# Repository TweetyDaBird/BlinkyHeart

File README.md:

# BlinkyRGB
Blinky RGB Keychains in various shapes and sizes.

Uses an Microchip ATTINY85 MCU, and is powered by a CR2032 coin cell.

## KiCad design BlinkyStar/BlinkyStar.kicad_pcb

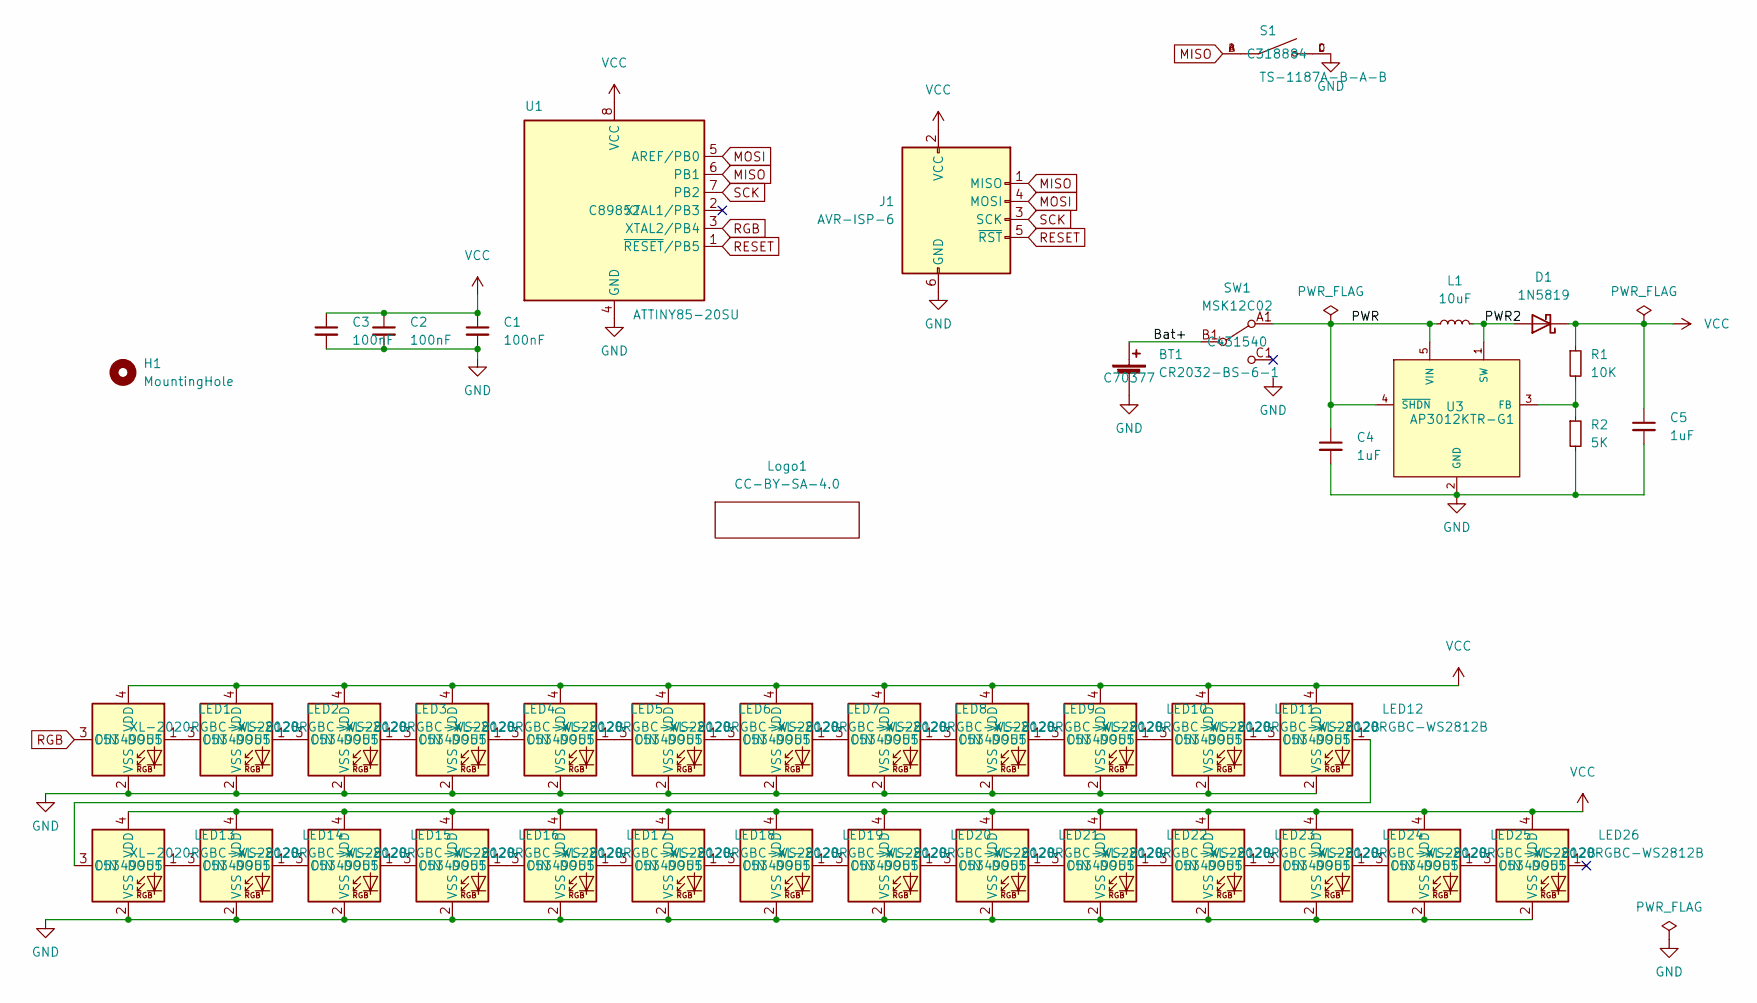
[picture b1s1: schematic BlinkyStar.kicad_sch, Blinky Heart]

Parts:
BT1: CR2032-BS-6-1; BAT_CR2032-BS-6-1; LCSC C70377
C1, C2, C3: 100nF; C_0603_1608Metric_Pad1.08x0.95mm_HandSolder; LCSC C14663
C4, C5: 1uF; C_0603_1608Metric_Pad1.08x0.95mm_HandSolder; LCSC C15849
D1: 1N5819; D_SMA; LCSC C437199
H1: MountingHole; MountingHole_3.2mm_M3
J1: AVR-ISP-6; PinHeader_2x03_P2.54mm_Vertical
L1: 10uF; IND_FDSD0420-H-100M=P3; LCSC C1329533
LED1, LED2, LED3, LED4, LED5, LED6, LED7, LED8, LED9, LED10, LED11, LED12, LED13, LED14, LED15, LED16, LED17, LED18, LED19, LED20, LED21, LED22, LED23, LED24, LED25, LED26: XL-2020RGBC-WS2812B; LED_WS2812-2020; LCSC C5349955
Logo1: CC-BY-SA-4.0; CC_BY_SA_40
R1: 10K; R_0603_1608Metric_Pad0.98x0.95mm_HandSolder; LCSC C3017715
R2: 5K; R_0603_1608Metric_Pad0.98x0.95mm_HandSolder; LCSC C2828621
S1: TS-1187A-B-A-B; SW_TS-1187A-B-A-B; PARTREV A0; LCSC C318884
SW1: MSK12C02; LCSC C431540
U1: ATTINY85-20SU; SOIC-8W_5.3x5.3mm_P1.27mm; LCSC C89852
U3: AP3012KTR-G1; SOT95P280X145-5N; PARTREV 1.6; LCSC C102618

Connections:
/Bat+: BT1.1 (+), SW1.B1 (COM)
/PWR: C4.1, L1.1, SW1.A1 (A), U3.4 (~SHDN), U3.5 (VIN)
/PWR2: D1.2 (A), L1.2, U3.1 (SW)
GND: BT1.2 (-), C1.2, C2.2, C3.2, C4.2, C5.2, J1.6 (GND), LED1.2 (VSS), LED2.2 (VSS), LED3.2 (VSS), LED4.2 (VSS), LED5.2 (VSS), LED6.2 (VSS), LED7.2 (VSS), LED8.2 (VSS), LED9.2 (VSS), LED10.2 (VSS), LED11.2 (VSS), LED12.2 (VSS), LED13.2 (VSS), LED14.2 (VSS), LED15.2 (VSS), LED16.2 (VSS), LED17.2 (VSS), LED18.2 (VSS), LED19.2 (VSS), LED20.2 (VSS), LED21.2 (VSS), LED22.2 (VSS), LED23.2 (VSS), LED24.2 (VSS), LED25.2 (VSS), LED26.2 (VSS), R2.2, S1.C, S1.D, SW1.MP (GND), U1.4 (GND), U3.2 (GND)
MISO: J1.1 (MISO), S1.A, S1.B, U1.6 (PB1)
MOSI: J1.4 (MOSI), U1.5 (AREF/PB0)
unnamed: LED1.1 (DOUT), LED2.3 (DIN)
unnamed: LED2.1 (DOUT), LED3.3 (DIN)
unnamed: LED3.1 (DOUT), LED4.3 (DIN)
unnamed: LED4.1 (DOUT), LED5.3 (DIN)
unnamed: LED5.1 (DOUT), LED6.3 (DIN)
unnamed: LED6.1 (DOUT), LED7.3 (DIN)
unnamed: LED7.1 (DOUT), LED8.3 (DIN)
unnamed: LED8.1 (DOUT), LED9.3 (DIN)
unnamed: LED10.1 (DOUT), LED11.3 (DIN)
unnamed: LED9.1 (DOUT), LED10.3 (DIN)
unnamed: LED11.1 (DOUT), LED12.3 (DIN)
unnamed: LED12.1 (DOUT), LED13.3 (DIN)
unnamed: LED13.1 (DOUT), LED14.3 (DIN)
unnamed: LED14.1 (DOUT), LED15.3 (DIN)
unnamed: LED15.1 (DOUT), LED16.3 (DIN)
unnamed: LED16.1 (DOUT), LED17.3 (DIN)
unnamed: LED17.1 (DOUT), LED18.3 (DIN)
unnamed: LED18.1 (DOUT), LED19.3 (DIN)
unnamed: LED19.1 (DOUT), LED20.3 (DIN)
unnamed: LED20.1 (DOUT), LED21.3 (DIN)
unnamed: LED21.1 (DOUT), LED22.3 (DIN)
unnamed: LED22.1 (DOUT), LED23.3 (DIN)
unnamed: LED23.1 (DOUT), LED24.3 (DIN)
unnamed: LED24.1 (DOUT), LED25.3 (DIN)
unnamed: LED25.1 (DOUT), LED26.3 (DIN)
unnamed: R1.2, R2.1, U3.3 (FB)
RESET: J1.5 (~RST), U1.1 (~RESET/PB5)
RGB: LED1.3 (DIN), U1.3 (XTAL2/PB4)
SCK: J1.3 (SCK), U1.7 (PB2)
VCC: C1.1, C2.1, C3.1, C5.1, D1.1 (K), J1.2 (VCC), LED1.4 (VDD), LED2.4 (VDD), LED3.4 (VDD), LED4.4 (VDD), LED5.4 (VDD), LED6.4 (VDD), LED7.4 (VDD), LED8.4 (VDD), LED9.4 (VDD), LED10.4 (VDD), LED11.4 (VDD), LED12.4 (VDD), LED13.4 (VDD), LED14.4 (VDD), LED15.4 (VDD), LED16.4 (VDD), LED17.4 (VDD), LED18.4 (VDD), LED19.4 (VDD), LED20.4 (VDD), LED21.4 (VDD), LED22.4 (VDD), LED23.4 (VDD), LED24.4 (VDD), LED25.4 (VDD), LED26.4 (VDD), R1.1, U1.8 (VCC)

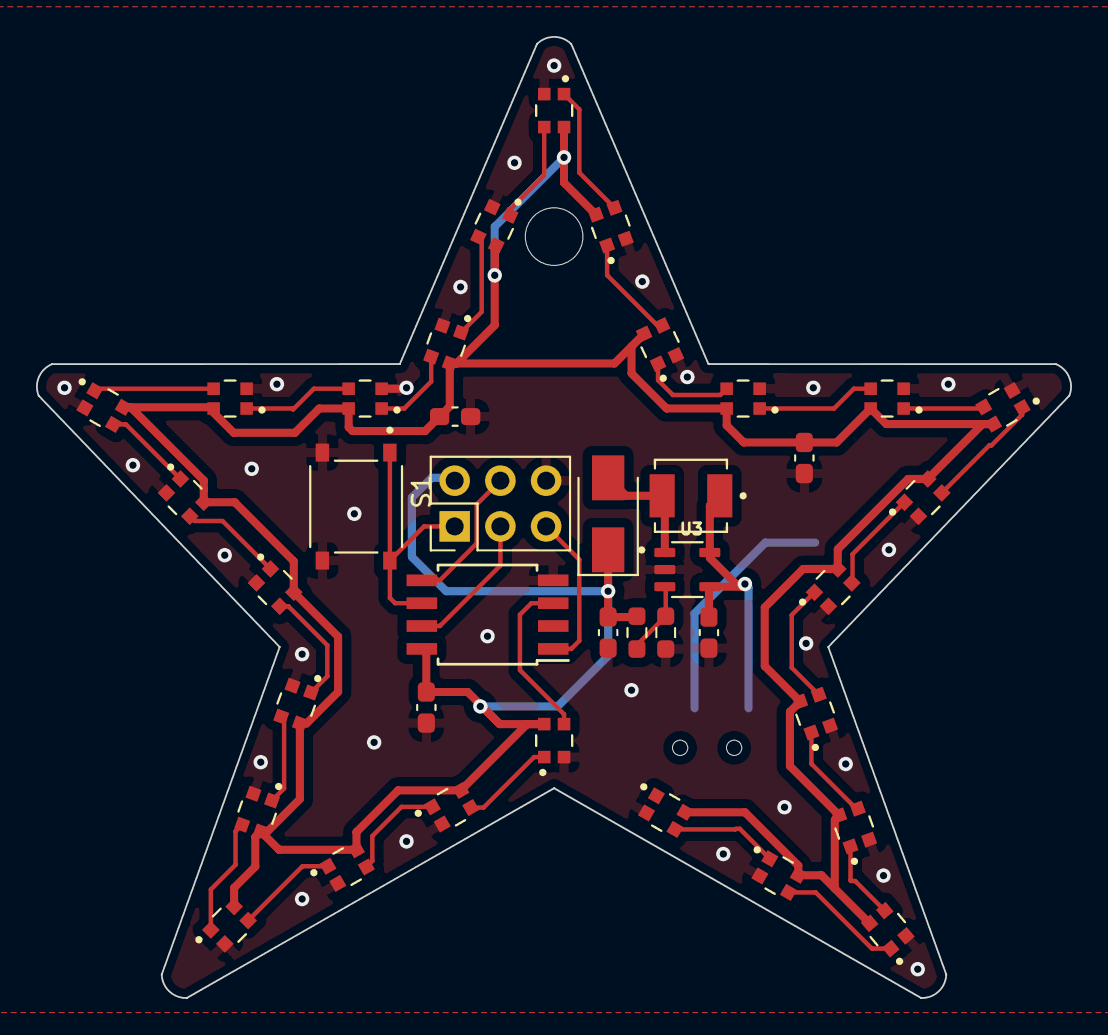
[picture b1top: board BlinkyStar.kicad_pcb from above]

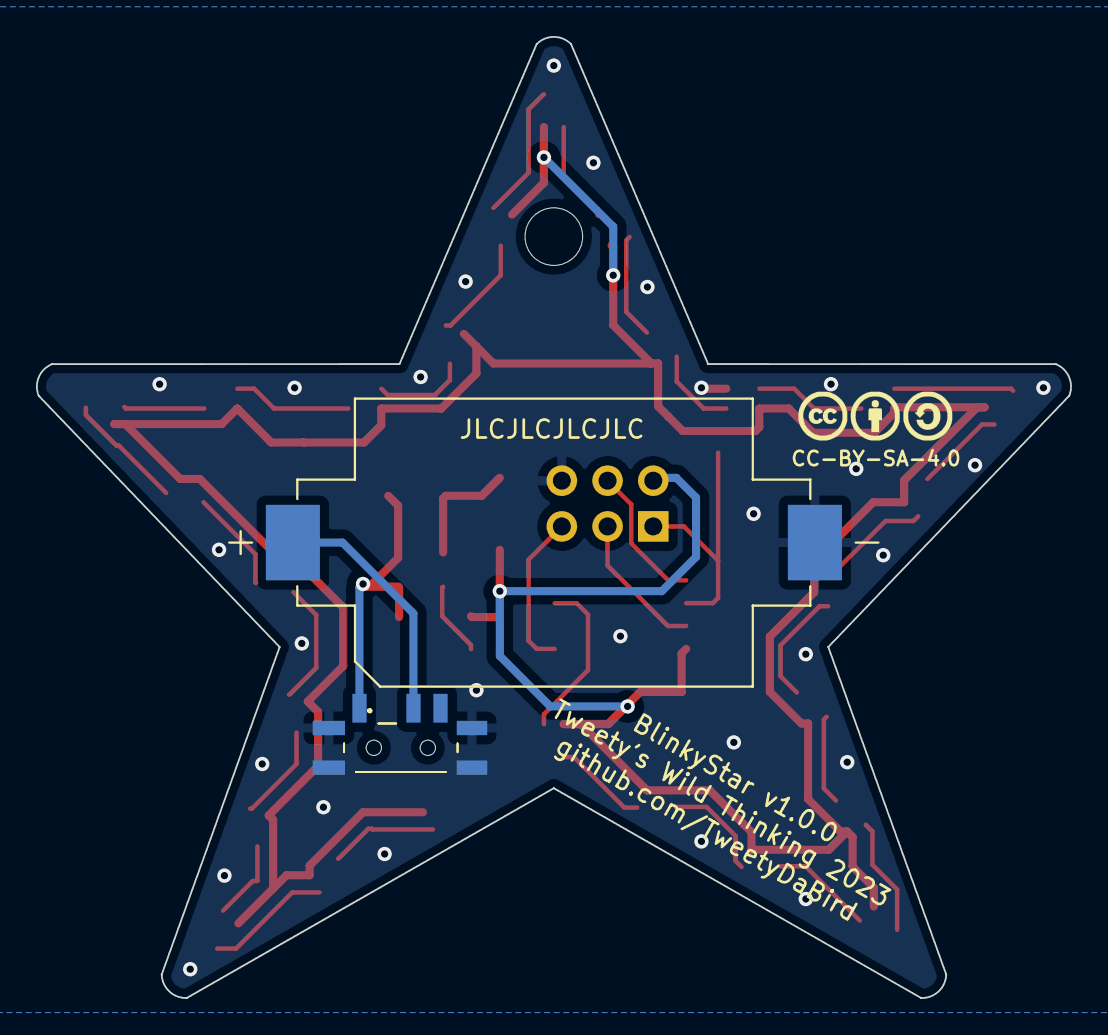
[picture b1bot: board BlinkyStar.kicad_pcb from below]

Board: 2 copper layers, 57.5 x 53.4 mm, 43 parts (3 on the bottom side), 36 nets.

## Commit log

2023-02-06 silkscreen update
2023-02-06 Create LICENSE
2023-02-07 Added BlinkyStar
2023-02-07 BlinkyStar BOM
2023-02-07 Added Blinky Smiley

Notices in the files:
BlinkyStar/BlinkyStar.kicad_pcb:
Licensed under Creative Commons BY-SA 4.0 International
